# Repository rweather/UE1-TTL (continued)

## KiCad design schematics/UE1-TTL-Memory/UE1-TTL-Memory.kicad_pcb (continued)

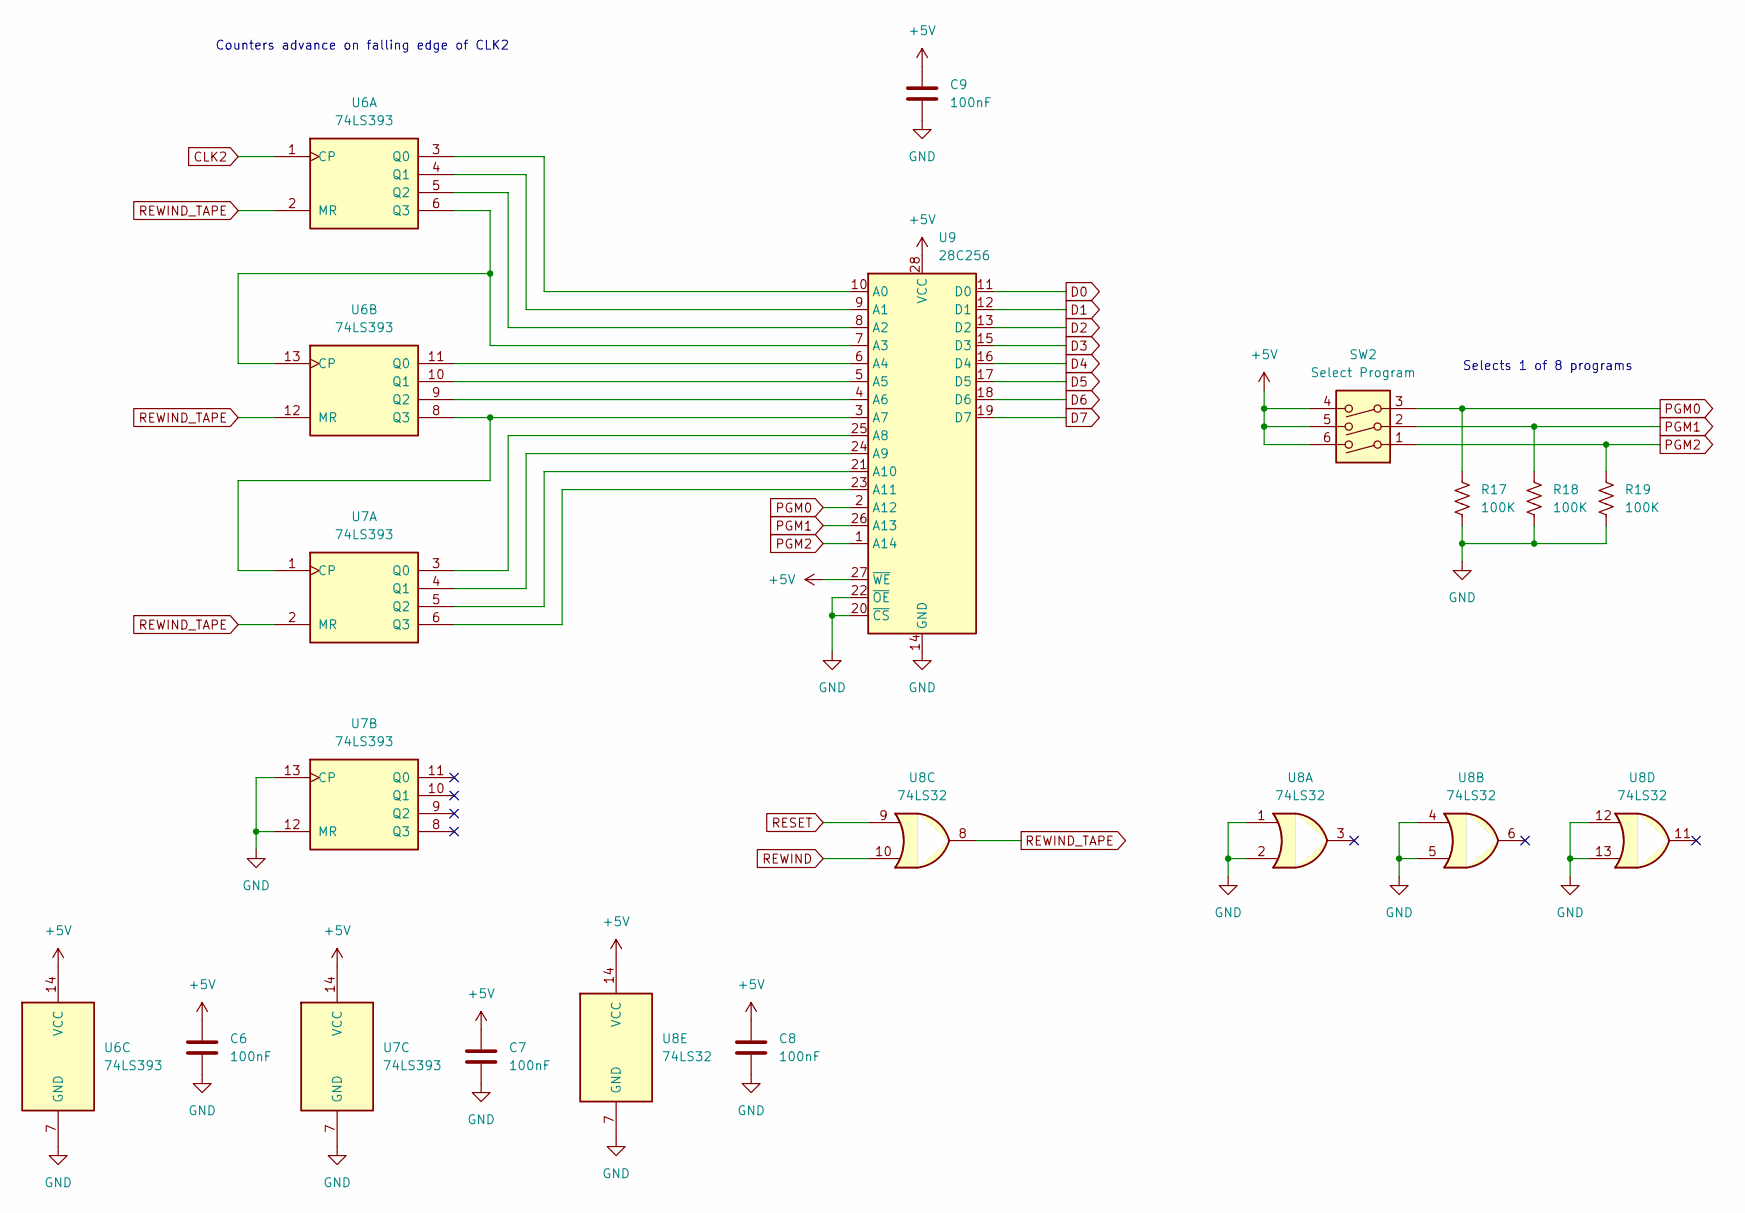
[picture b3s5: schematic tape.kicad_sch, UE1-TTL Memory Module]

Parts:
C6, C7, C8, C9: 100nF; C_Disc_D5.0mm_W2.5mm_P5.00mm
R17, R18, R19: 100K; R_Axial_DIN0207_L6.3mm_D2.5mm_P7.62mm_Horizontal
SW2: Select Program; SW_DIP_SPSTx03_Slide_6.7x9.18mm_W7.62mm_P2.54mm_LowProfile
U6, U7: 74LS393; DIP-14_W7.62mm
U8: 74LS32; DIP-14_W7.62mm
U9: 28C256; DIP-28_W15.24mm_Socket

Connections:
+5V: C6.1, C7.1, C8.1, C9.1, SW2.4, SW2.5, SW2.6, U6.14 (VCC), U7.14 (VCC), U8.14 (VCC), U9.27 (~WE), U9.28 (VCC); also elsewhere on the board
CLK2: U6.1 (CP); also elsewhere on the board
D0: U9.11 (D0); also elsewhere on the board
D1: U9.12 (D1); also elsewhere on the board
D2: U9.13 (D2); also elsewhere on the board
D3: U9.15 (D3); also elsewhere on the board
D4: U9.16 (D4); also elsewhere on the board
D5: U9.17 (D5); also elsewhere on the board
D6: U9.18 (D6); also elsewhere on the board
D7: U9.19 (D7); also elsewhere on the board
GND: C6.2, C7.2, C8.2, C9.2, R17.2, R18.2, R19.2, U6.7 (GND), U7.7 (GND), U7.12 (MR), U7.13 (CP), U8.1, U8.2, U8.4, U8.5, U8.7 (GND), U8.12, U8.13, U9.14 (GND), U9.20 (~CS), U9.22 (~OE); also elsewhere on the board
unnamed: U6.3 (Q0), U9.10 (A0)
unnamed: U6.4 (Q1), U9.9 (A1)
unnamed: U6.5 (Q2), U9.8 (A2)
unnamed: U6.6 (Q3), U6.13 (CP), U9.7 (A3)
unnamed: U6.11 (Q0), U9.6 (A4)
unnamed: U6.10 (Q1), U9.5 (A5)
unnamed: U6.9 (Q2), U9.4 (A6)
unnamed: U6.8 (Q3), U7.1 (CP), U9.3 (A7)
unnamed: U7.3 (Q0), U9.25 (A8)
unnamed: U7.4 (Q1), U9.24 (A9)
unnamed: U7.5 (Q2), U9.21 (A10)
unnamed: U7.6 (Q3), U9.23 (A11)
PGM0: R17.1, SW2.3, U9.2 (A12)
PGM1: R18.1, SW2.2, U9.26 (A13)
PGM2: R19.1, SW2.1, U9.1 (A14)
RESET: U8.9; also elsewhere on the board
REWIND: U8.10; also elsewhere on the board
REWIND_TAPE: U6.2 (MR), U6.12 (MR), U7.2 (MR), U8.8

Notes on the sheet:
Selects 1 of 8 programs
Counters advance on falling edge of CLK2

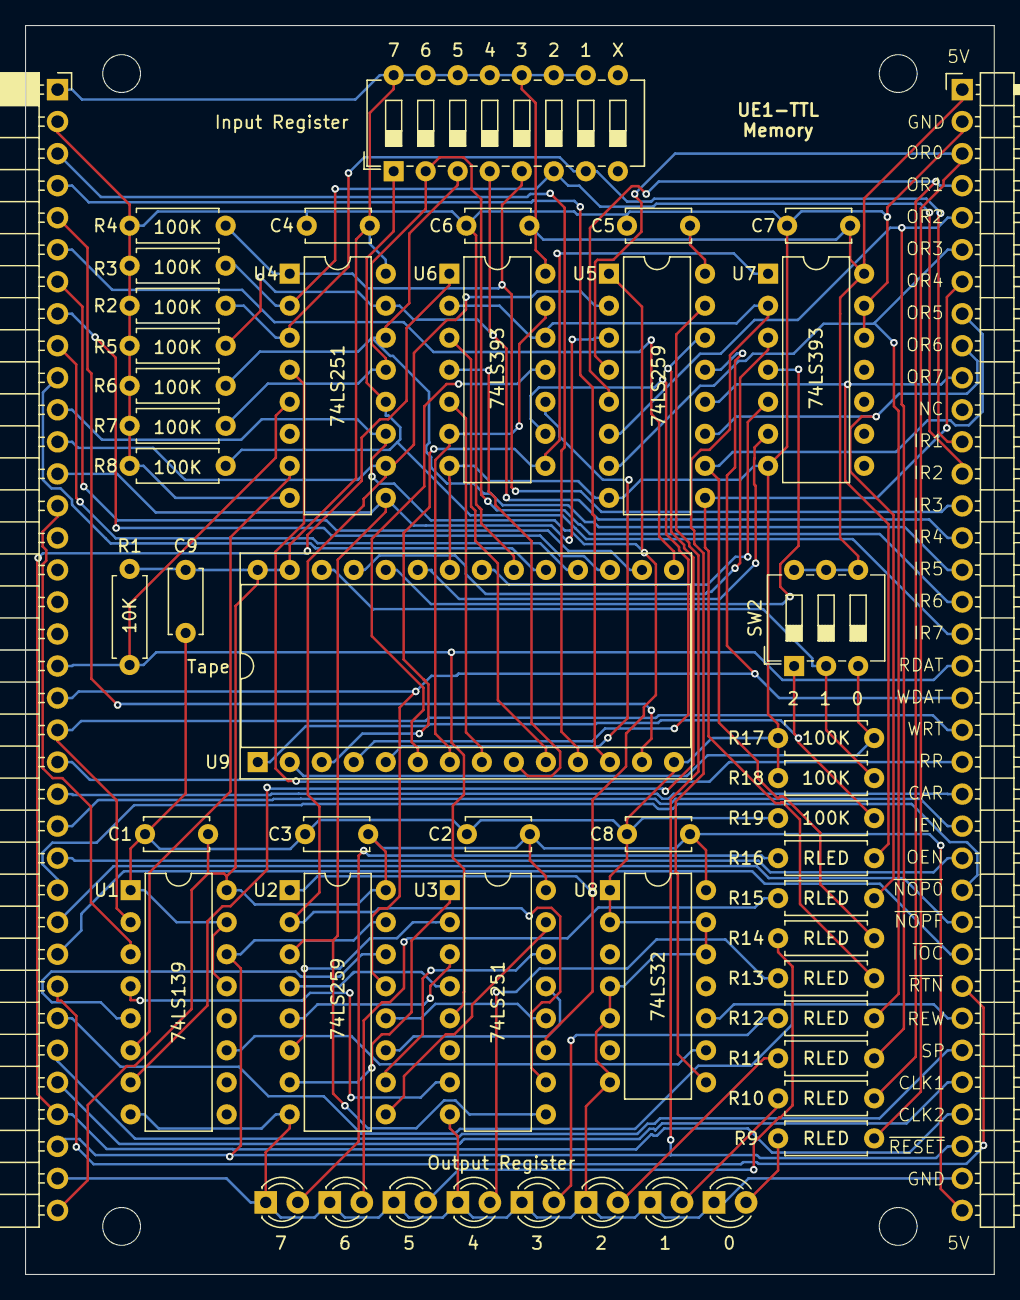
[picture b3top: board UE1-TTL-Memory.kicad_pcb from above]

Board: 2 copper layers, 76.8 x 99.1 mm, 53 parts (0 on the bottom side), 82 nets.

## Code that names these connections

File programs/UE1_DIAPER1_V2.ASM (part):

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;

;
; Initialize the registers: RR = 1, CAR = 0, IEN = 1, OEN = 1
;
; The "ONE" instruction is done twice, just in case the skip register
; is set to 1 when the program starts.  Otherwise we skip the init!
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;
; 0/1 + 1 = 1/0
;
ADD  RR         ; CAR = 0, RR = 1, 1 + 1 = 2
SKZ  RR         ; Fail the test if RR = 1.
NOPF SR0
;
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
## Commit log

2025-06-26 Schematic for the UE14500-TTL
2025-06-26 Schematics for the memory board
2025-06-27 Clock and Front Panel schematic
2025-06-27 Add a tape "REWIND" opcode to reset the PC early
2025-06-27 Make some renderings of the computer
2025-06-28 Lay out CPU board
2025-06-28 Lay out clock board
2025-06-28 Lay out memory board
2025-06-28 Change 74LS151 to 74LS251
2025-06-28 Update the 3D renderings
2025-06-28 Add the README and LICENSE
2025-06-29 Generate Gerbers
2025-06-29 Change capacitor in reset RC circuit to 1uF
2025-07-04 Start writing the theory of operation
2025-07-04 Assembling and testing the clock board
2025-07-05 Assembling and testing the processor board
2025-07-05 Finish writing the theory of operation manual
2025-07-05 Document the signals on the edge connectors
2025-07-11 Copy UE14500-TTL schematic to UE14500-TTL-V1
2025-07-12 Fix WRITE gating on processor board
2025-07-12 Test ROM
2025-07-12 Test procedure for the memory board
2025-07-12 Document how to do single-stepping off-board
2025-07-21 Work around some issues with the REWIND instruction
2025-07-21 Rabbit example for 8x8 LED dot matrix displays
2025-07-24 Update the CPU schematic with V2 modifications
2025-07-24 Update the clock schematic with V2 modifications
2025-07-26 Update the documentation to reflect version 2 and document the bodges
2025-08-19 1-D Life example from decle - program 6
